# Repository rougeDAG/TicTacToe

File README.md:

<h1>TicTacToe</h1>

A first year graded project I submitted for my course in Digital System Design (Winter Semester, Vellore Institue of Technology, Chennai). This is a Tic Tac Toe game that uses only digital logic to play the game. PCB Design was done on KiCad , an open source PCB Design software. I simulated the circuit in another open source digital simulator called Digital.exe (which is based on another software called Logisim) by Helmut Neemann which I downloaded from his GitHub repository.
Digital.exe helped me immensely in my project as I cannot have simulated my project without this software for free. Here is his GitHub repository: [github.com/hneemann/Digital](#github.com/hneemann/Digital)

_________________________________________________________________________________________________________________________________________________________________________________________________________________________________________________

Now for KiCad, I used another free and open source software called Freerouting by Andras Fuchs to auto-route my wire connections in KiCad. Here is that GitHub repository: [github.com/freerouting/freerouting](#github.com/freerouting/freerouting)

Again it would've been painstaking to connect all the components pinouts invidivually , thus this software also played a massive role in saving time as I had to submit my project in a short span of time.

 To open the files in KiCad, go to KiCad, click on File->Open Project and then open the file folder thats downloaded and click on "DSD_Project" of the file type "KiCad Project 9.0". Updated versions may come in the future but it still should work the same.

 To open the files in Digital.exe, go to Digital, click on Open and click on "dsd_project_digital.dig".

_________________________________________________________________________________________________________________________________________________________________________________________________________________________________________________

<h1>Sneek Peek into Digital.exe simulation:</h1>

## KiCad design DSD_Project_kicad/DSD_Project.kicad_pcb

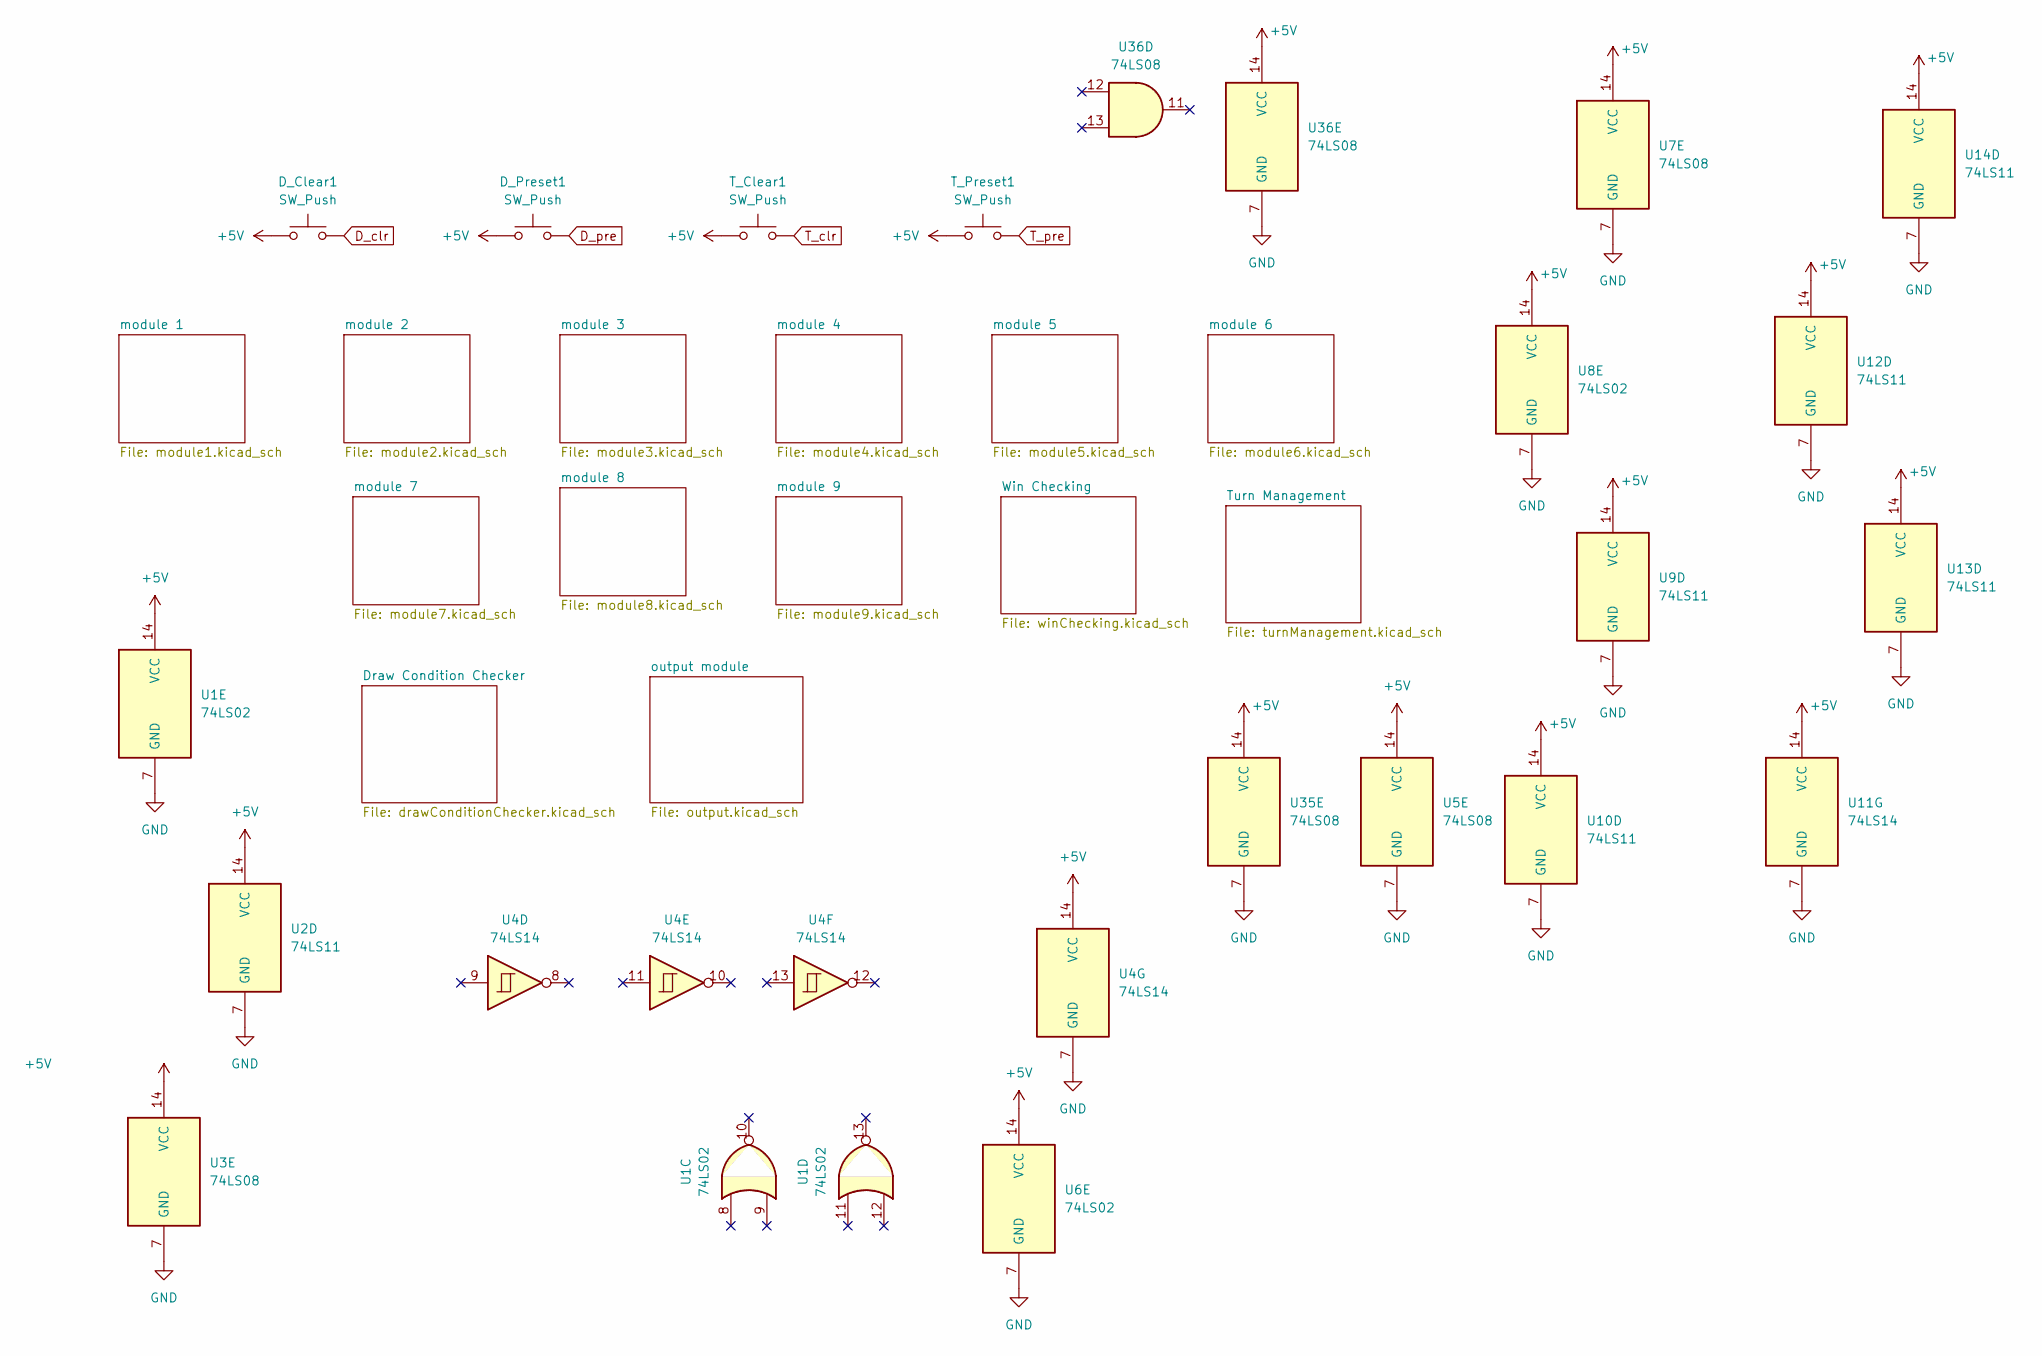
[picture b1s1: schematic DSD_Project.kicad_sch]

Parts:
D_Clear1: SW_Push; SW_SPDT_PCM12
D_Preset1: SW_Push; SW_SPDT_PCM12
T_Clear1: SW_Push; SW_SPDT_PCM12
T_Preset1: SW_Push; SW_SPDT_PCM12
U1, U6, U8: 74LS02; DIP-14_W7.62mm
U2, U9, U10, U12, U13, U14: 74LS11; DIP-14_W7.62mm
U3, U5, U7, U35, U36: 74LS08; DIP-14_W7.62mm
U4, U11: 74LS14; DIP-14_W7.62mm

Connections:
+5V: D_Clear1.1, D_Preset1.1, T_Clear1.1, T_Preset1.1, U1.14 (VCC), U2.14 (VCC), U3.14 (VCC), U4.14 (VCC), U5.14 (VCC), U6.14 (VCC), U7.14 (VCC), U8.14 (VCC), U9.14 (VCC), U10.14 (VCC), U11.14 (VCC), U12.14 (VCC), U13.14 (VCC), U14.14 (VCC), U35.14 (VCC), U36.14 (VCC); also elsewhere on the board
D_clr: D_Clear1.2; also elsewhere on the board
D_pre: D_Preset1.2; also elsewhere on the board
GND: U1.7 (GND), U2.7 (GND), U3.7 (GND), U4.7 (GND), U5.7 (GND), U6.7 (GND), U7.7 (GND), U8.7 (GND), U9.7 (GND), U10.7 (GND), U11.7 (GND), U12.7 (GND), U13.7 (GND), U14.7 (GND), U35.7 (GND), U36.7 (GND); also elsewhere on the board
T_clr: T_Clear1.2; also elsewhere on the board
T_pre: T_Preset1.2; also elsewhere on the board

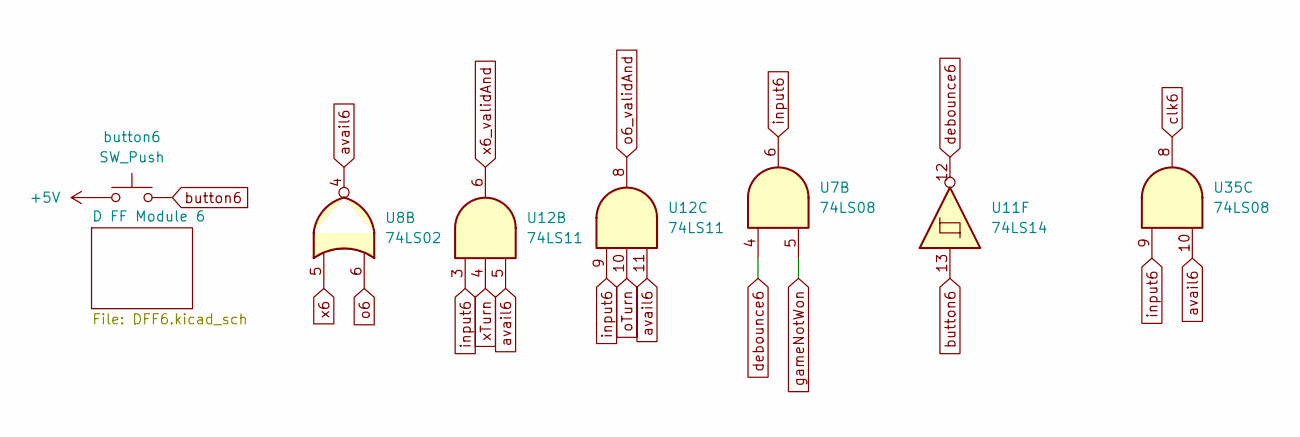
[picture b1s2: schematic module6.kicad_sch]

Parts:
U7, U35: 74LS08; DIP-14_W7.62mm
U8: 74LS02; DIP-14_W7.62mm
U11: 74LS14; DIP-14_W7.62mm
U12: 74LS11; DIP-14_W7.62mm
button6: SW_Push; SW_PUSH_6mm

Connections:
+5V: button6.1; also elsewhere on the board
avail6: U8.4, U12.5, U12.11, U35.10; also elsewhere on the board
button6: U11.13, button6.2
clk6: U35.8; also elsewhere on the board
debounce6: U7.4, U11.12
gameNotWon: U7.5; also elsewhere on the board
input6: U7.6, U12.3, U12.9, U35.9
o6: U8.6; also elsewhere on the board
o6_validAnd: U12.8; also elsewhere on the board
oTurn: U12.10; also elsewhere on the board
x6: U8.5; also elsewhere on the board
x6_validAnd: U12.6; also elsewhere on the board
xTurn: U12.4; also elsewhere on the board

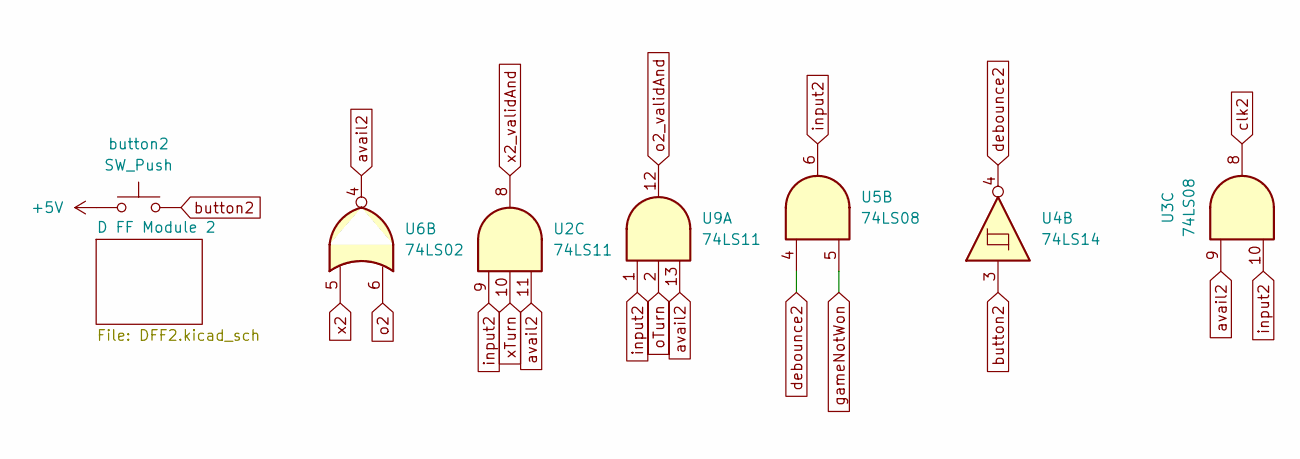
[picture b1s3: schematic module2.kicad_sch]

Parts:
U2, U9: 74LS11; DIP-14_W7.62mm
U3, U5: 74LS08; DIP-14_W7.62mm
U4: 74LS14; DIP-14_W7.62mm
U6: 74LS02; DIP-14_W7.62mm
button2: SW_Push; SW_PUSH_6mm

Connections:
+5V: button2.1; also elsewhere on the board
avail2: U2.11, U3.9, U6.4, U9.13; also elsewhere on the board
button2: U4.3, button2.2
clk2: U3.8; also elsewhere on the board
debounce2: U4.4, U5.4
gameNotWon: U5.5; also elsewhere on the board
input2: U2.9, U3.10, U5.6, U9.1
o2: U6.6; also elsewhere on the board
o2_validAnd: U9.12; also elsewhere on the board
oTurn: U9.2; also elsewhere on the board
x2: U6.5; also elsewhere on the board
x2_validAnd: U2.8; also elsewhere on the board
xTurn: U2.10; also elsewhere on the board

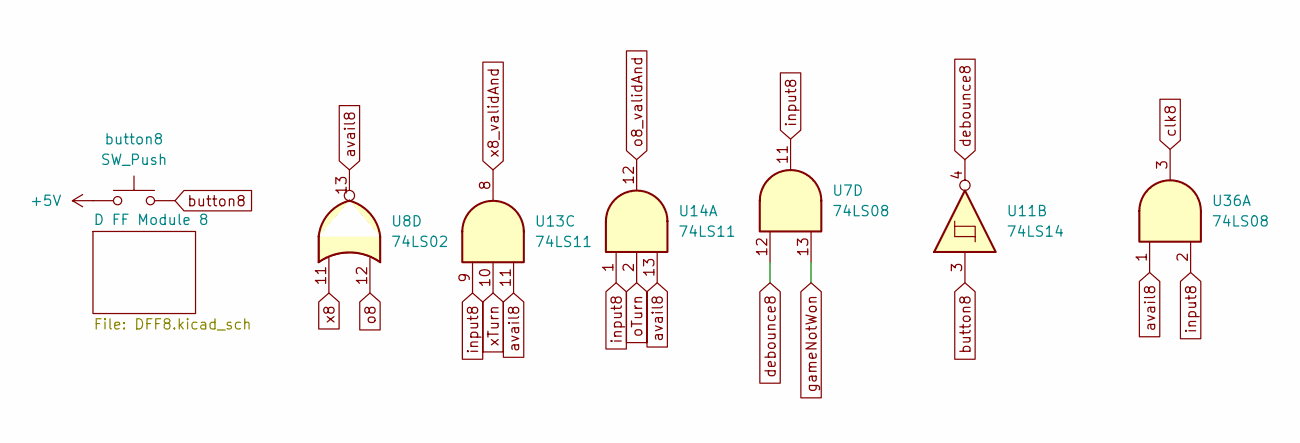
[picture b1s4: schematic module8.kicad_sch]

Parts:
U7, U36: 74LS08; DIP-14_W7.62mm
U8: 74LS02; DIP-14_W7.62mm
U11: 74LS14; DIP-14_W7.62mm
U13, U14: 74LS11; DIP-14_W7.62mm
button8: SW_Push; SW_PUSH_6mm

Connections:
+5V: button8.1; also elsewhere on the board
avail8: U8.13, U13.11, U14.13, U36.1; also elsewhere on the board
button8: U11.3, button8.2
clk8: U36.3; also elsewhere on the board
debounce8: U7.12, U11.4
gameNotWon: U7.13; also elsewhere on the board
input8: U7.11, U13.9, U14.1, U36.2
o8: U8.12; also elsewhere on the board
o8_validAnd: U14.12; also elsewhere on the board
oTurn: U14.2; also elsewhere on the board
x8: U8.11; also elsewhere on the board
x8_validAnd: U13.8; also elsewhere on the board
xTurn: U13.10; also elsewhere on the board

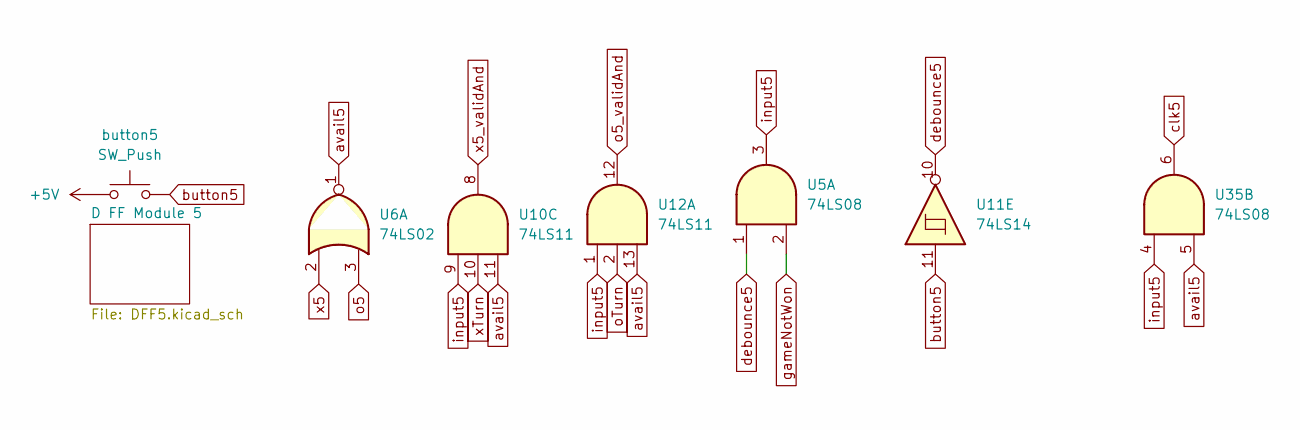
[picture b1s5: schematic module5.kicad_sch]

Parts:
U5, U35: 74LS08; DIP-14_W7.62mm
U6: 74LS02; DIP-14_W7.62mm
U10, U12: 74LS11; DIP-14_W7.62mm
U11: 74LS14; DIP-14_W7.62mm
button5: SW_Push; SW_PUSH_6mm

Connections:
+5V: button5.1; also elsewhere on the board
avail5: U6.1, U10.11, U12.13, U35.5; also elsewhere on the board
button5: U11.11, button5.2
clk5: U35.6; also elsewhere on the board
debounce5: U5.1, U11.10
gameNotWon: U5.2; also elsewhere on the board
input5: U5.3, U10.9, U12.1, U35.4
o5: U6.3; also elsewhere on the board
o5_validAnd: U12.12; also elsewhere on the board
oTurn: U12.2; also elsewhere on the board
x5: U6.2; also elsewhere on the board
x5_validAnd: U10.8; also elsewhere on the board
xTurn: U10.10; also elsewhere on the board

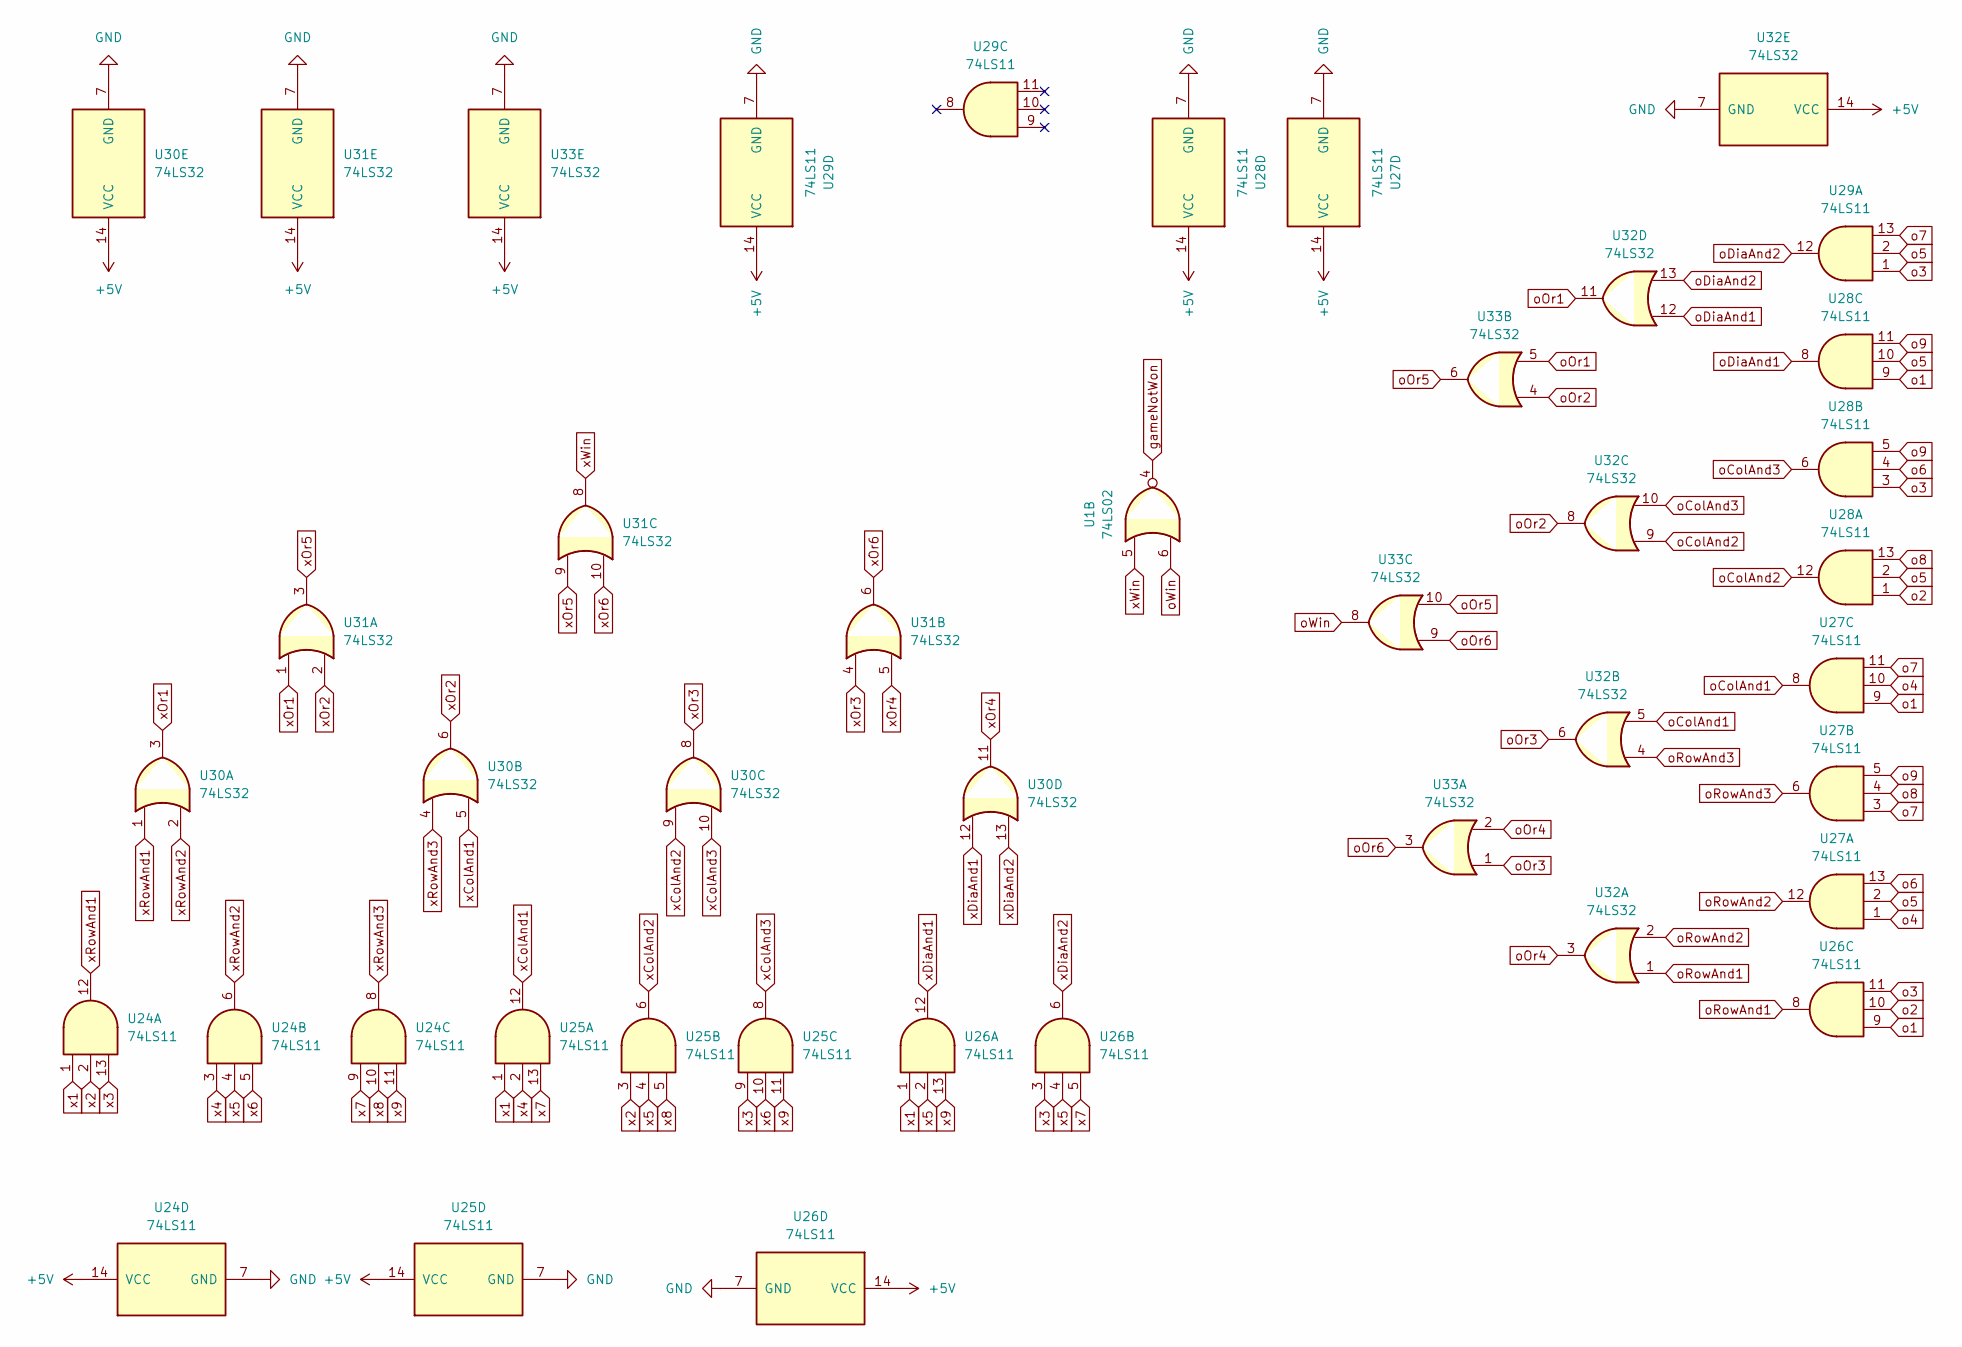
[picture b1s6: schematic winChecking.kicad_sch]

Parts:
U1: 74LS02; DIP-14_W7.62mm
U24, U25, U26, U27, U28, U29: 74LS11; DIP-14_W7.62mm
U30, U31, U32, U33: 74LS32; DIP-14_W7.62mm

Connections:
+5V: U24.14 (VCC), U25.14 (VCC), U26.14 (VCC), U27.14 (VCC), U28.14 (VCC), U29.14 (VCC), U30.14 (VCC), U31.14 (VCC), U32.14 (VCC), U33.14 (VCC); also elsewhere on the board
GND: U24.7 (GND), U25.7 (GND), U26.7 (GND), U27.7 (GND), U28.7 (GND), U29.7 (GND), U30.7 (GND), U31.7 (GND), U32.7 (GND), U33.7 (GND); also elsewhere on the board
gameNotWon: U1.4; also elsewhere on the board
o1: U26.9, U27.9, U28.9; also elsewhere on the board
o2: U26.10, U28.1; also elsewhere on the board
o3: U26.11, U28.3, U29.1; also elsewhere on the board
o4: U27.1, U27.10; also elsewhere on the board
o5: U27.2, U28.2, U28.10, U29.2; also elsewhere on the board
o6: U27.13, U28.4; also elsewhere on the board
o7: U27.3, U27.11, U29.13; also elsewhere on the board
o8: U27.4, U28.13; also elsewhere on the board
o9: U27.5, U28.5, U28.11; also elsewhere on the board
oColAnd1: U27.8, U32.5
oColAnd2: U28.12, U32.9
oColAnd3: U28.6, U32.10
oDiaAnd1: U28.8, U32.12
oDiaAnd2: U29.12, U32.13
oOr1: U32.11, U33.5
oOr2: U32.8, U33.4
oOr3: U32.6, U33.1
oOr4: U32.3, U33.2
oOr5: U33.6, U33.10
oOr6: U33.3, U33.9
oRowAnd1: U26.8, U32.1
oRowAnd2: U27.12, U32.2
oRowAnd3: U27.6, U32.4
oWin: U1.6, U33.8; also elsewhere on the board
x1: U24.1, U25.1, U26.1; also elsewhere on the board
x2: U24.2, U25.3; also elsewhere on the board
x3: U24.13, U25.9, U26.3; also elsewhere on the board
x4: U24.3, U25.2; also elsewhere on the board
x5: U24.4, U25.4, U26.2, U26.4; also elsewhere on the board
x6: U24.5, U25.10; also elsewhere on the board
x7: U24.9, U25.13, U26.5; also elsewhere on the board
x8: U24.10, U25.5; also elsewhere on the board
x9: U24.11, U25.11, U26.13; also elsewhere on the board
xColAnd1: U25.12, U30.5
xColAnd2: U25.6, U30.9
xColAnd3: U25.8, U30.10
xDiaAnd1: U26.12, U30.12
xDiaAnd2: U26.6, U30.13
xOr1: U30.3, U31.1
xOr2: U30.6, U31.2
xOr3: U30.8, U31.4
xOr4: U30.11, U31.5
xOr5: U31.3, U31.9
xOr6: U31.6, U31.10
xRowAnd1: U24.12, U30.1
xRowAnd2: U24.6, U30.2
xRowAnd3: U24.8, U30.4
xWin: U1.5, U31.8; also elsewhere on the board

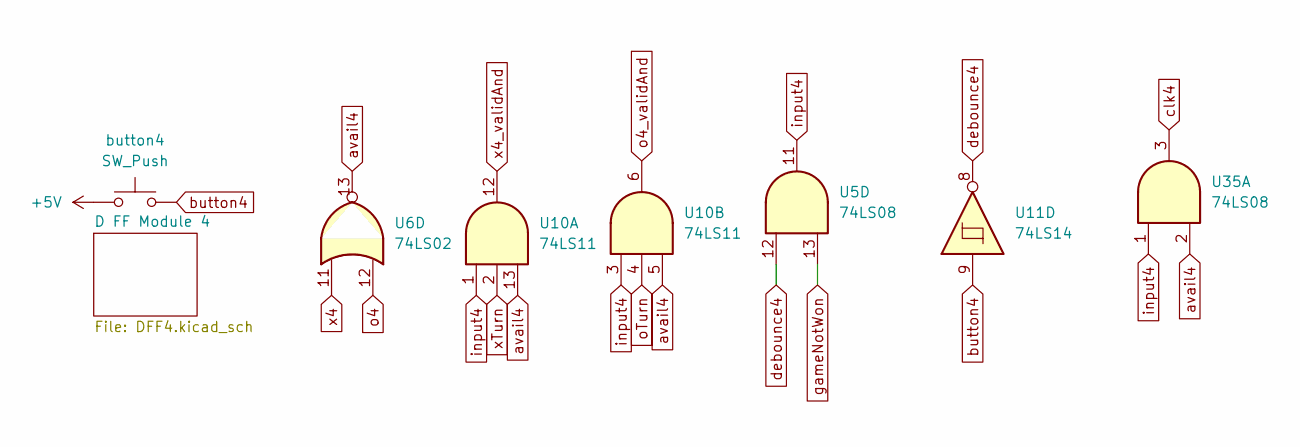
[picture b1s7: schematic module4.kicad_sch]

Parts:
U5, U35: 74LS08; DIP-14_W7.62mm
U6: 74LS02; DIP-14_W7.62mm
U10: 74LS11; DIP-14_W7.62mm
U11: 74LS14; DIP-14_W7.62mm
button4: SW_Push; SW_PUSH_6mm

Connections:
+5V: button4.1; also elsewhere on the board
avail4: U6.13, U10.5, U10.13, U35.2; also elsewhere on the board
button4: U11.9, button4.2
clk4: U35.3; also elsewhere on the board
debounce4: U5.12, U11.8
gameNotWon: U5.13; also elsewhere on the board
input4: U5.11, U10.1, U10.3, U35.1
o4: U6.12; also elsewhere on the board
o4_validAnd: U10.6; also elsewhere on the board
oTurn: U10.4; also elsewhere on the board
x4: U6.11; also elsewhere on the board
x4_validAnd: U10.12; also elsewhere on the board
xTurn: U10.2; also elsewhere on the board

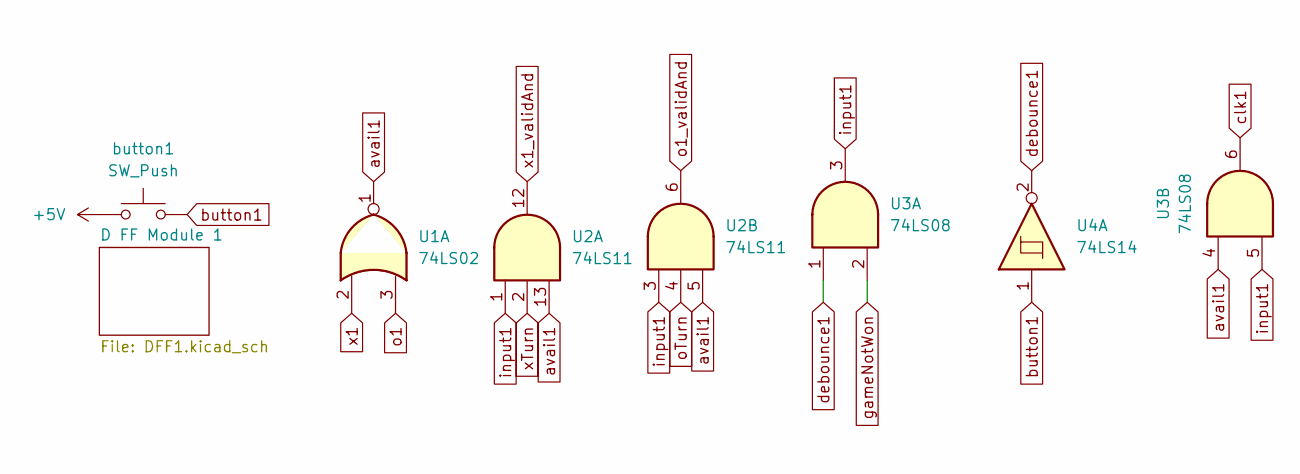
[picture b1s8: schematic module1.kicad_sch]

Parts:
U1: 74LS02; DIP-14_W7.62mm
U2: 74LS11; DIP-14_W7.62mm
U3: 74LS08; DIP-14_W7.62mm
U4: 74LS14; DIP-14_W7.62mm
button1: SW_Push; SW_PUSH_6mm

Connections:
+5V: button1.1; also elsewhere on the board
avail1: U1.1, U2.5, U2.13, U3.4; also elsewhere on the board
button1: U4.1, button1.2
clk1: U3.6; also elsewhere on the board
debounce1: U3.1, U4.2
gameNotWon: U3.2; also elsewhere on the board
input1: U2.1, U2.3, U3.3, U3.5
o1: U1.3; also elsewhere on the board
o1_validAnd: U2.6; also elsewhere on the board
oTurn: U2.4; also elsewhere on the board
x1: U1.2; also elsewhere on the board
x1_validAnd: U2.12; also elsewhere on the board
xTurn: U2.2; also elsewhere on the board

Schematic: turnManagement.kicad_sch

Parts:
U31, U33, U37, U38: 74LS32; DIP-14_W7.62mm
U34: 74LS76; DIP-16_W7.62mm

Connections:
+5V: U34.4 (J), U34.5 (VCC), U34.16 (K), U37.14 (VCC), U38.14 (VCC); also elsewhere on the board
GND: U34.13 (GND), U37.7 (GND), U38.7 (GND); also elsewhere on the board
T_clr: U34.3 (~R); also elsewhere on the board
T_pre: U34.2 (~S); also elsewhere on the board
clk1: U31.12; also elsewhere on the board
clk2: U31.13; also elsewhere on the board
clk3: U33.12; also elsewhere on the board
clk4: U33.13; also elsewhere on the board
clk5: U37.1; also elsewhere on the board
clk6: U37.2; also elsewhere on the board
clk7: U37.4; also elsewhere on the board
clk8: U37.5; also elsewhere on the board
clk9: U37.10; also elsewhere on the board
clkOr1: U31.11, U38.4
clkOr2: U33.11, U37.12
clkOr3: U37.3, U37.13
clkOr4: U37.6, U37.9
clkOr5: U37.11, U38.1
clkOr6: U37.8, U38.2
clkOr7: U38.3, U38.5
oTurn: U34.14 (~Q); also elsewhere on the board
tclk: U34.1 (C), U38.6
xTurn: U34.15 (Q); also elsewhere on the board

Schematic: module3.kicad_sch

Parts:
U3, U5: 74LS08; DIP-14_W7.62mm
U4: 74LS14; DIP-14_W7.62mm
U6: 74LS02; DIP-14_W7.62mm
U9: 74LS11; DIP-14_W7.62mm
button3: SW_Push; SW_PUSH_6mm

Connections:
+5V: button3.1; also elsewhere on the board
avail3: U3.12, U6.10, U9.5, U9.11; also elsewhere on the board
button3: U4.5, button3.2
clk3: U3.11; also elsewhere on the board
debounce3: U4.6, U5.9
gameNotWon: U5.10; also elsewhere on the board
input3: U3.13, U5.8, U9.3, U9.9
o3: U6.9; also elsewhere on the board
o3_validAnd: U9.8; also elsewhere on the board
oTurn: U9.10; also elsewhere on the board
x3: U6.8; also elsewhere on the board
x3_validAnd: U9.6; also elsewhere on the board
xTurn: U9.4; also elsewhere on the board

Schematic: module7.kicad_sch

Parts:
U7, U35: 74LS08; DIP-14_W7.62mm
U8: 74LS02; DIP-14_W7.62mm
U11: 74LS14; DIP-14_W7.62mm
U13: 74LS11; DIP-14_W7.62mm
button7: SW_Push; SW_PUSH_6mm

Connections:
+5V: button7.1; also elsewhere on the board
avail7: U8.10, U13.5, U13.13, U35.13; also elsewhere on the board
button7: U11.1, button7.2
clk7: U35.11; also elsewhere on the board
debounce7: U7.9, U11.2
gameNotWon: U7.10; also elsewhere on the board
input7: U7.8, U13.1, U13.3, U35.12
o7: U8.9; also elsewhere on the board
o7_validAnd: U13.6; also elsewhere on the board
oTurn: U13.4; also elsewhere on the board
x7: U8.8; also elsewhere on the board
x7_validAnd: U13.12; also elsewhere on the board
xTurn: U13.2; also elsewhere on the board

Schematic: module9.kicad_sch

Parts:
U7, U36: 74LS08; DIP-14_W7.62mm
U8: 74LS02; DIP-14_W7.62mm
U11: 74LS14; DIP-14_W7.62mm
U14: 74LS11; DIP-14_W7.62mm
button9: SW_Push; SW_PUSH_6mm

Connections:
+5V: button9.1; also elsewhere on the board
avail9: U8.1, U14.5, U14.11, U36.5; also elsewhere on the board
button9: U11.5, button9.2
clk9: U36.6; also elsewhere on the board
debounce9: U7.1, U11.6
gameNotWon: U7.2; also elsewhere on the board
input9: U7.3, U14.3, U14.9, U36.4
o9: U8.3; also elsewhere on the board
o9_validAnd: U14.8; also elsewhere on the board
oTurn: U14.10; also elsewhere on the board
x9: U8.2; also elsewhere on the board
x9_validAnd: U14.6; also elsewhere on the board
xTurn: U14.4; also elsewhere on the board

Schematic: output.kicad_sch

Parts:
BT1: 12V; TerminalBlock_Phoenix_MKDS-3-2-5.08_1x02_P5.08mm_Horizontal
DRAW1: LED; LED_D3.0mm
O_WON1: LED; LED_D3.0mm
Q1, Q2, Q3: NPN; TO-92_Inline
R1, R3, R5: 6800; R_Axial_DIN0309_L9.0mm_D3.2mm_P12.70mm_Horizontal
R2, R4, R6: 150; R_Axial_DIN0207_L6.3mm_D2.5mm_P7.62mm_Horizontal
U40: XL1509-5.0; SOIC-8_3.9x4.9mm_P1.27mm
X_WON1: LED; LED_D3.0mm
buckEn1: SW_Push; SW_SPDT_PCM12

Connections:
+5V: R2.2, R4.2, R6.2, U40.2 (OUT), U40.3 (FB), buckEn1.2; also elsewhere on the board
GND: BT1.2 (-), Q1.3 (E), Q2.3 (E), Q3.3 (E), U40.5 (GND), U40.6 (GND), U40.7 (GND), U40.8 (GND); also elsewhere on the board
unnamed: BT1.1 (+), U40.1 (VIN)
unnamed: DRAW1.2 (A), R6.1
unnamed: DRAW1.1 (K), Q3.1 (C)
unnamed: O_WON1.2 (A), R4.1
unnamed: O_WON1.1 (K), Q2.1 (C)
unnamed: Q1.2 (B), R1.2
unnamed: Q1.1 (C), X_WON1.1 (K)
unnamed: Q2.2 (B), R3.2
unnamed: Q3.2 (B), R5.2
unnamed: U40.4 (~EN), buckEn1.1
unnamed: R2.1, X_WON1.2 (A)
draw: R5.1; also elsewhere on the board
oWin: R3.1; also elsewhere on the board
xWin: R1.1; also elsewhere on the board

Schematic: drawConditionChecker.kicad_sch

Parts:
U29: 74LS11; DIP-14_W7.62mm
U36: 74LS08; DIP-14_W7.62mm
U39: 74LS27; DIP-14_W7.62mm

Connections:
+5V: U39.14 (VCC); also elsewhere on the board
GND: U39.7 (GND); also elsewhere on the board
avail1: U39.1; also elsewhere on the board
avail2: U39.2; also elsewhere on the board
avail3: U39.13; also elsewhere on the board
avail4: U39.3; also elsewhere on the board
avail5: U39.4; also elsewhere on the board
avail6: U39.5; also elsewhere on the board
avail7: U39.9; also elsewhere on the board
avail8: U39.10; also elsewhere on the board
avail9: U39.11; also elsewhere on the board
draw: U36.8; also elsewhere on the board
drawAnd: U29.6, U36.9
gameNotWon: U36.10; also elsewhere on the board
nor1: U29.5, U39.12
nor2: U29.4, U39.6
nor3: U29.3, U39.8

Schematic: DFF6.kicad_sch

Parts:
U20: 74LS74; DIP-14_W7.62mm

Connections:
+5V: U20.2 (D), U20.12 (D), U20.14 (VCC); also elsewhere on the board
D_clr: U20.1 (~R), U20.13 (~R); also elsewhere on the board
D_pre: U20.4 (~S), U20.10 (~S); also elsewhere on the board
GND: U20.7 (GND); also elsewhere on the board
o6: U20.9 (Q); also elsewhere on the board
o6_validAnd: U20.11 (C); also elsewhere on the board
x6: U20.5 (Q); also elsewhere on the board
x6_validAnd: U20.3 (C); also elsewhere on the board

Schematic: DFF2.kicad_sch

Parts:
U16: 74LS74; DIP-14_W7.62mm

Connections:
+5V: U16.2 (D), U16.12 (D), U16.14 (VCC); also elsewhere on the board
D_clr: U16.1 (~R), U16.13 (~R); also elsewhere on the board
D_pre: U16.4 (~S), U16.10 (~S); also elsewhere on the board
GND: U16.7 (GND); also elsewhere on the board
o2: U16.9 (Q); also elsewhere on the board
o2_validAnd: U16.11 (C); also elsewhere on the board
x2: U16.5 (Q); also elsewhere on the board
x2_validAnd: U16.3 (C); also elsewhere on the board

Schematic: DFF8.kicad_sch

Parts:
U22: 74LS74; DIP-14_W7.62mm

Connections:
+5V: U22.2 (D), U22.12 (D), U22.14 (VCC); also elsewhere on the board
D_clr: U22.1 (~R), U22.13 (~R); also elsewhere on the board
D_pre: U22.4 (~S), U22.10 (~S); also elsewhere on the board
GND: U22.7 (GND); also elsewhere on the board
o8: U22.9 (Q); also elsewhere on the board
o8_validAnd: U22.11 (C); also elsewhere on the board
x8: U22.5 (Q); also elsewhere on the board
x8_validAnd: U22.3 (C); also elsewhere on the board

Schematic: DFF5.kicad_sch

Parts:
U19: 74LS74; DIP-14_W7.62mm

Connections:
+5V: U19.2 (D), U19.12 (D), U19.14 (VCC); also elsewhere on the board
D_clr: U19.1 (~R), U19.13 (~R); also elsewhere on the board
D_pre: U19.4 (~S), U19.10 (~S); also elsewhere on the board
GND: U19.7 (GND); also elsewhere on the board
o5: U19.9 (Q); also elsewhere on the board
o5_validAnd: U19.11 (C); also elsewhere on the board
x5: U19.5 (Q); also elsewhere on the board
x5_validAnd: U19.3 (C); also elsewhere on the board

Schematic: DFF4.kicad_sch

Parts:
U18: 74LS74; DIP-14_W7.62mm

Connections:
+5V: U18.2 (D), U18.12 (D), U18.14 (VCC); also elsewhere on the board
D_clr: U18.1 (~R), U18.13 (~R); also elsewhere on the board
D_pre: U18.4 (~S), U18.10 (~S); also elsewhere on the board
GND: U18.7 (GND); also elsewhere on the board
o4: U18.9 (Q); also elsewhere on the board
o4_validAnd: U18.11 (C); also elsewhere on the board
x4: U18.5 (Q); also elsewhere on the board
x4_validAnd: U18.3 (C); also elsewhere on the board

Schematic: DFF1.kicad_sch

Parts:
U15: 74LS74; DIP-14_W7.62mm

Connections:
+5V: U15.2 (D), U15.12 (D), U15.14 (VCC); also elsewhere on the board
D_clr: U15.1 (~R), U15.13 (~R); also elsewhere on the board
D_pre: U15.4 (~S), U15.10 (~S); also elsewhere on the board
GND: U15.7 (GND); also elsewhere on the board
o1: U15.9 (Q); also elsewhere on the board
o1_validAnd: U15.11 (C); also elsewhere on the board
x1: U15.5 (Q); also elsewhere on the board
x1_validAnd: U15.3 (C); also elsewhere on the board

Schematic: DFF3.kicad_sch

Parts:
U17: 74LS74; DIP-14_W7.62mm

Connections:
+5V: U17.2 (D), U17.12 (D), U17.14 (VCC); also elsewhere on the board
D_clr: U17.1 (~R), U17.13 (~R); also elsewhere on the board
D_pre: U17.4 (~S), U17.10 (~S); also elsewhere on the board
GND: U17.7 (GND); also elsewhere on the board
o3: U17.9 (Q); also elsewhere on the board
o3_validAnd: U17.11 (C); also elsewhere on the board
x3: U17.5 (Q); also elsewhere on the board
x3_validAnd: U17.3 (C); also elsewhere on the board

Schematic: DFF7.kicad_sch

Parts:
U21: 74LS74; DIP-14_W7.62mm

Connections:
+5V: U21.2 (D), U21.12 (D), U21.14 (VCC); also elsewhere on the board
D_clr: U21.1 (~R), U21.13 (~R); also elsewhere on the board
D_pre: U21.4 (~S), U21.10 (~S); also elsewhere on the board
GND: U21.7 (GND); also elsewhere on the board
o7: U21.9 (Q); also elsewhere on the board
o7_validAnd: U21.11 (C); also elsewhere on the board
x7: U21.5 (Q); also elsewhere on the board
x7_validAnd: U21.3 (C); also elsewhere on the board

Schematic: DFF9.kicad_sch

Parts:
U23: 74LS74; DIP-14_W7.62mm

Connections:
+5V: U23.2 (D), U23.12 (D), U23.14 (VCC); also elsewhere on the board
D_clr: U23.1 (~R), U23.13 (~R); also elsewhere on the board
D_pre: U23.4 (~S), U23.10 (~S); also elsewhere on the board
GND: U23.7 (GND); also elsewhere on the board
o9: U23.9 (Q); also elsewhere on the board
o9_validAnd: U23.11 (C); also elsewhere on the board
x9: U23.5 (Q); also elsewhere on the board
x9_validAnd: U23.3 (C); also elsewhere on the board

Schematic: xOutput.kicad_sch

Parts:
Q4, Q5, Q6, Q7, Q8, Q9, Q10, Q11, Q12: NPN; TO-92_Inline
R7, R9, R11, R13, R15, R17, R19, R21, R23: 6800; R_Axial_DIN0309_L9.0mm_D3.2mm_P12.70mm_Horizontal
R8, R10, R12, R14, R16, R18, R20, R22, R24: 150; R_Axial_DIN0207_L6.3mm_D2.5mm_P7.62mm_Horizontal
x1, x2, x3, x4, x5, x6, x7, x8, x9: LED; LED_D3.0mm

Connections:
+5V: R8.2, R10.2, R12.2, R14.2, R16.2, R18.2, R20.2, R22.2, R24.2; also elsewhere on the board
GND: Q4.3 (E), Q5.3 (E), Q6.3 (E), Q7.3 (E), Q8.3 (E), Q9.3 (E), Q10.3 (E), Q11.3 (E), Q12.3 (E); also elsewhere on the board
unnamed: Q4.2 (B), R7.2
unnamed: Q4.1 (C), x1.1 (K)
unnamed: Q5.2 (B), R9.2
unnamed: Q5.1 (C), x2.1 (K)
unnamed: Q6.2 (B), R11.2
unnamed: Q6.1 (C), x3.1 (K)
unnamed: Q7.2 (B), R13.2
unnamed: Q7.1 (C), x4.1 (K)
unnamed: Q8.2 (B), R15.2
unnamed: Q8.1 (C), x5.1 (K)
unnamed: Q9.2 (B), R17.2
unnamed: Q9.1 (C), x6.1 (K)
unnamed: Q10.2 (B), R19.2
unnamed: Q10.1 (C), x7.1 (K)
unnamed: Q11.2 (B), R21.2
unnamed: Q11.1 (C), x8.1 (K)
unnamed: Q12.2 (B), R23.2
unnamed: Q12.1 (C), x9.1 (K)
unnamed: R8.1, x1.2 (A)
unnamed: R10.1, x2.2 (A)
unnamed: R12.1, x3.2 (A)
unnamed: R14.1, x4.2 (A)
unnamed: R16.1, x5.2 (A)
unnamed: R18.1, x6.2 (A)
unnamed: R20.1, x7.2 (A)
unnamed: R22.1, x8.2 (A)
unnamed: R24.1, x9.2 (A)
x1: R7.1; also elsewhere on the board
x2: R9.1; also elsewhere on the board
x3: R11.1; also elsewhere on the board
x4: R13.1; also elsewhere on the board
x5: R15.1; also elsewhere on the board
x6: R17.1; also elsewhere on the board
x7: R19.1; also elsewhere on the board
x8: R21.1; also elsewhere on the board
x9: R23.1; also elsewhere on the board

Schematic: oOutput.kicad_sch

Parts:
Q13, Q14, Q15, Q16, Q17, Q18, Q19, Q20, Q21: NPN; TO-92_Inline
R25, R26, R27, R31, R32, R33, R37, R38, R39: 6800; R_Axial_DIN0309_L9.0mm_D3.2mm_P12.70mm_Horizontal
R28, R29, R30, R34, R35, R36, R40, R41, R42: 150; R_Axial_DIN0207_L6.3mm_D2.5mm_P7.62mm_Horizontal
o1, o2, o3, o4, o5, o6, o7, o8, o9: LED; LED_D3.0mm

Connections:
+5V: R28.2, R29.2, R30.2, R34.2, R35.2, R36.2, R40.2, R41.2, R42.2; also elsewhere on the board
GND: Q13.3 (E), Q14.3 (E), Q15.3 (E), Q16.3 (E), Q17.3 (E), Q18.3 (E), Q19.3 (E), Q20.3 (E), Q21.3 (E); also elsewhere on the board
unnamed: Q13.2 (B), R25.2
unnamed: Q13.1 (C), o7.1 (K)
unnamed: Q14.2 (B), R26.2
unnamed: Q14.1 (C), o4.1 (K)
unnamed: Q15.2 (B), R27.2
unnamed: Q15.1 (C), o1.1 (K)
unnamed: Q16.2 (B), R31.2
unnamed: Q16.1 (C), o8.1 (K)
unnamed: Q17.2 (B), R32.2
unnamed: Q17.1 (C), o5.1 (K)
unnamed: Q18.2 (B), R33.2
unnamed: Q18.1 (C), o2.1 (K)
unnamed: Q19.2 (B), R37.2
unnamed: Q19.1 (C), o9.1 (K)
unnamed: Q20.2 (B), R38.2
unnamed: Q20.1 (C), o6.1 (K)
unnamed: Q21.2 (B), R39.2
unnamed: Q21.1 (C), o3.1 (K)
unnamed: R30.1, o1.2 (A)
unnamed: R36.1, o2.2 (A)
unnamed: R42.1, o3.2 (A)
unnamed: R29.1, o4.2 (A)
unnamed: R35.1, o5.2 (A)
unnamed: R41.1, o6.2 (A)
unnamed: R28.1, o7.2 (A)
unnamed: R34.1, o8.2 (A)
unnamed: R40.1, o9.2 (A)
o1: R27.1; also elsewhere on the board
o2: R33.1; also elsewhere on the board
o3: R39.1; also elsewhere on the board
o4: R26.1; also elsewhere on the board
o5: R32.1; also elsewhere on the board
o6: R38.1; also elsewhere on the board
o7: R25.1; also elsewhere on the board
o8: R31.1; also elsewhere on the board
o9: R37.1; also elsewhere on the board
